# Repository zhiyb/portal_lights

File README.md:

# portal\_lights
Ingress portal lights

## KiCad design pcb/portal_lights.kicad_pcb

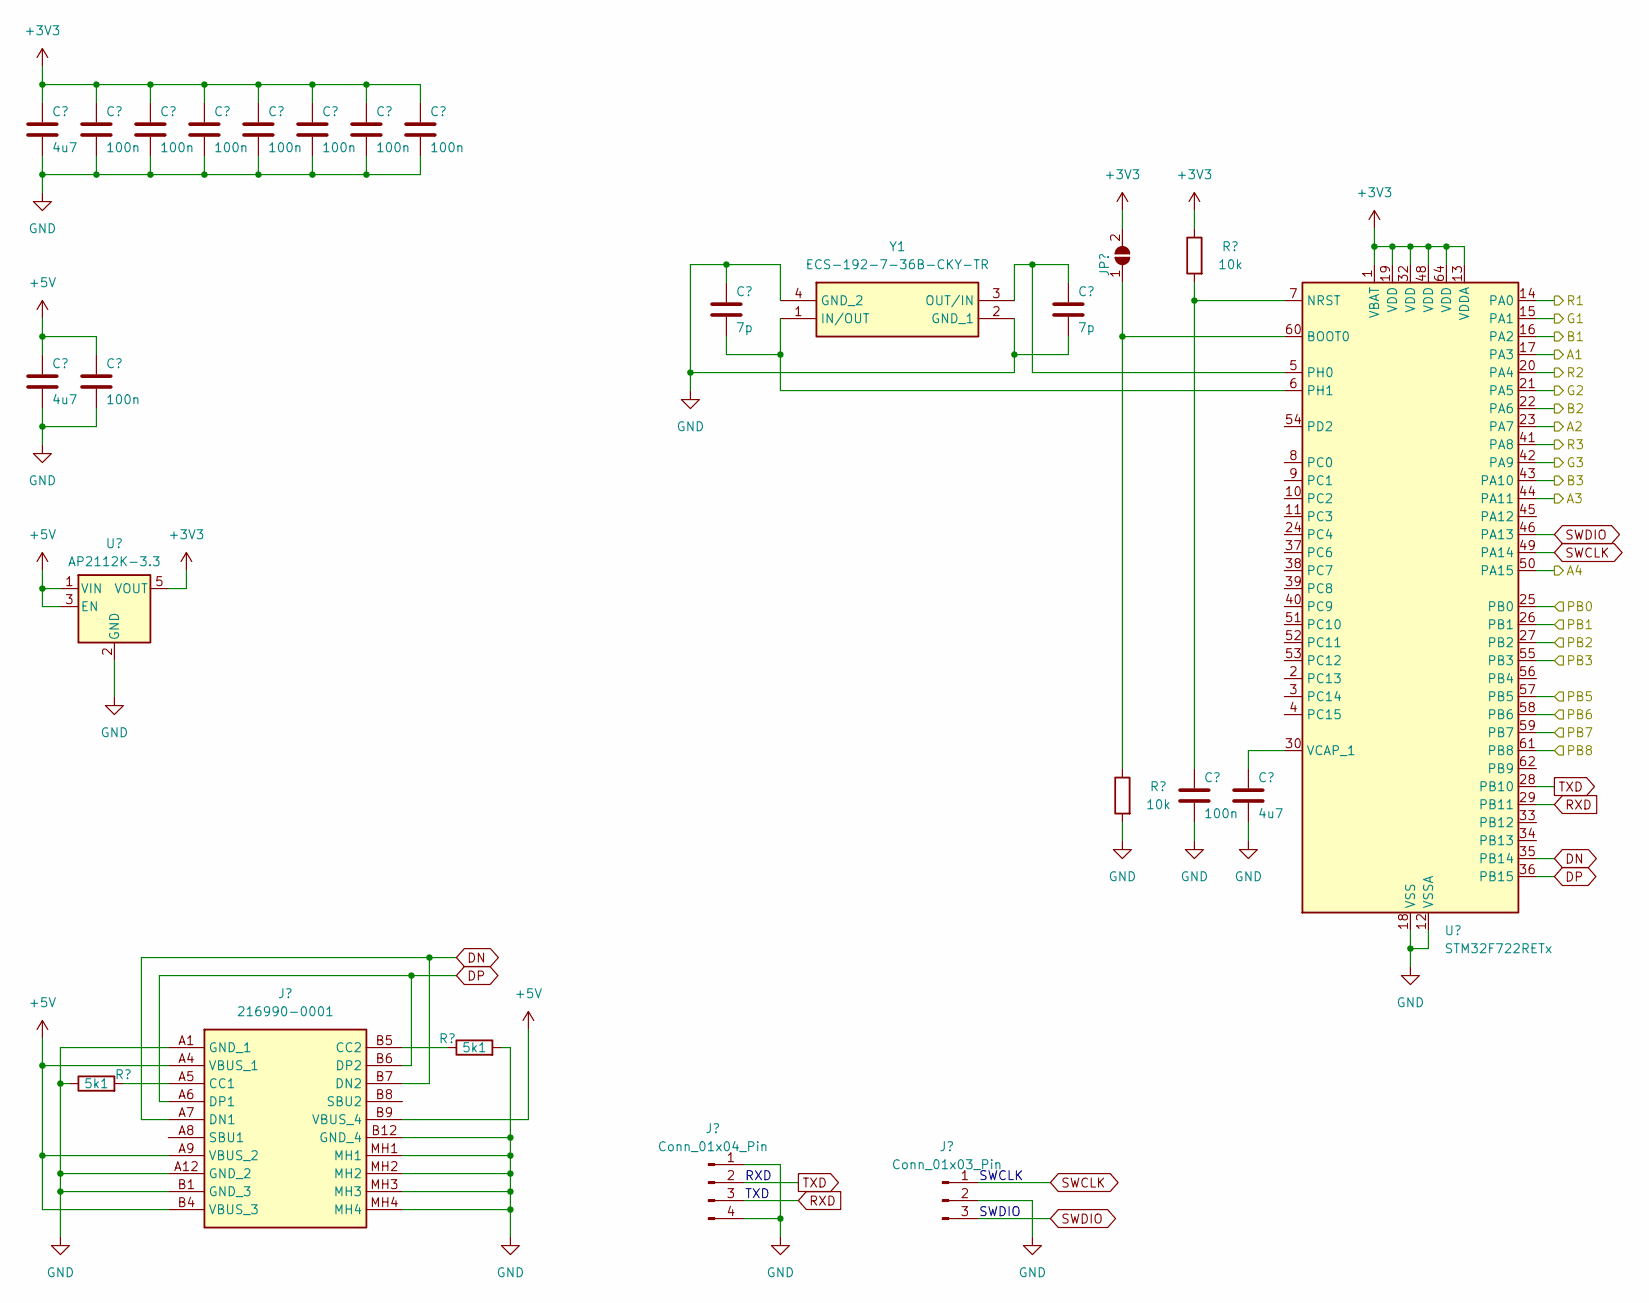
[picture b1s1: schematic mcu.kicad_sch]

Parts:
C1, C11, C14: 4u7; C_0402_1005Metric_Pad0.74x0.62mm_HandSolder
C2, C3, C4, C5, C6, C7, C8, C12, C13: 100n; C_0402_1005Metric_Pad0.74x0.62mm_HandSolder
C9, C10: 7p; C_0402_1005Metric_Pad0.74x0.62mm_HandSolder
J1: 216990-0001; 2169900001; Mouser Part Number 538-216990-0001
J2: Conn_01x04_Pin; PinHeader_1x04_P2.54mm_Vertical
J3: Conn_01x03_Pin; PinHeader_1x03_P2.54mm_Vertical
JP1: SolderJumper_2_Open; SolderJumper-2_P1.3mm_Open_RoundedPad1.0x1.5mm
R1, R2: 10k; R_0402_1005Metric_Pad0.72x0.64mm_HandSolder
R3, R4: 5k1; R_0402_1005Metric_Pad0.72x0.64mm_HandSolder
U1: AP2112K-3.3; SOT-23-5_HandSoldering
U2: STM32F722RETx; LQFP-64_10x10mm_P0.5mm
Y1: ECS-192-7-36B-CKY-TR; ECS192736BCKYTR; Mouser Part Number 520-192-7-36B-CKYT

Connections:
+3V3: C1.1, C2.1, C3.1, C4.1, C5.1, C6.1, C7.1, C8.1, JP1.2 (B), R1.1, U1.5 (VOUT), U2.1 (VBAT), U2.13 (VDDA), U2.19 (VDD), U2.32 (VDD), U2.48 (VDD), U2.64 (VDD); also elsewhere on the board
+5V: C11.1, C12.1, J1.A4 (VBUS_1), J1.A9 (VBUS_2), J1.B4 (VBUS_3), J1.B9 (VBUS_4), U1.1 (VIN), U1.3 (EN)
/IO/PB1: U2.25 (PB0); also elsewhere on the board
/IO/PB2: U2.26 (PB1); also elsewhere on the board
/IO/PB3: U2.27 (PB2); also elsewhere on the board
/IO/PB4: U2.55 (PB3); also elsewhere on the board
/IO/TB1: U2.57 (PB5); also elsewhere on the board
/IO/TB2: U2.58 (PB6); also elsewhere on the board
/IO/TB3: U2.59 (PB7); also elsewhere on the board
/IO/TB4: U2.61 (PB8); also elsewhere on the board
/Lights/A1: U2.17 (PA3); also elsewhere on the board
/Lights/A2: U2.23 (PA7); also elsewhere on the board
/Lights/A3: U2.44 (PA11); also elsewhere on the board
/Lights/A4: U2.50 (PA15); also elsewhere on the board
/Lights/B1: U2.16 (PA2); also elsewhere on the board
/Lights/B2: U2.22 (PA6); also elsewhere on the board
/Lights/B3: U2.43 (PA10); also elsewhere on the board
/Lights/G1: U2.15 (PA1); also elsewhere on the board
/Lights/G2: U2.21 (PA5); also elsewhere on the board
/Lights/G3: U2.42 (PA9); also elsewhere on the board
/Lights/R1: U2.14 (PA0); also elsewhere on the board
/Lights/R2: U2.20 (PA4); also elsewhere on the board
/Lights/R3: U2.41 (PA8); also elsewhere on the board
DN: J1.A7 (DN1), J1.B7 (DN2), U2.35 (PB14)
DP: J1.A6 (DP1), J1.B6 (DP2), U2.36 (PB15)
GND: C1.2, C2.2, C3.2, C4.2, C5.2, C6.2, C7.2, C8.2, C9.1, C10.2, C11.2, C12.2, C13.2, C14.2, J1.A1 (GND_1), J1.A12 (GND_2), J1.B1 (GND_3), J1.B12 (GND_4), J1.MH1, J1.MH2, J1.MH3, J1.MH4, J2.1, J2.4, J3.2, R2.2, R3.2, R4.1, U1.2 (GND), U2.12 (VSSA), U2.18 (VSS), U2.31 (VSS), U2.47 (VSS), U2.63 (VSS), Y1.2 (GND_1), Y1.4 (GND_2); also elsewhere on the board
unnamed: J1.A5 (CC1), R4.2
unnamed: J1.B5 (CC2), R3.1
unnamed: JP1.1 (A), R2.1, U2.60 (BOOT0)
unnamed: C13.1, R1.2, U2.7 (NRST)
unnamed: C10.1, U2.5 (PH0), Y1.3 (OUT/IN)
unnamed: C9.2, U2.6 (PH1), Y1.1 (IN/OUT)
unnamed: C14.1, U2.30 (VCAP_1)
RXD: J2.3, U2.29 (PB11)
SWCLK: J3.1, U2.49 (PA14)
SWDIO: J3.3, U2.46 (PA13)
TXD: J2.2, U2.28 (PB10)

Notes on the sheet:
RXD
SWCLK
TXD
SWDIO

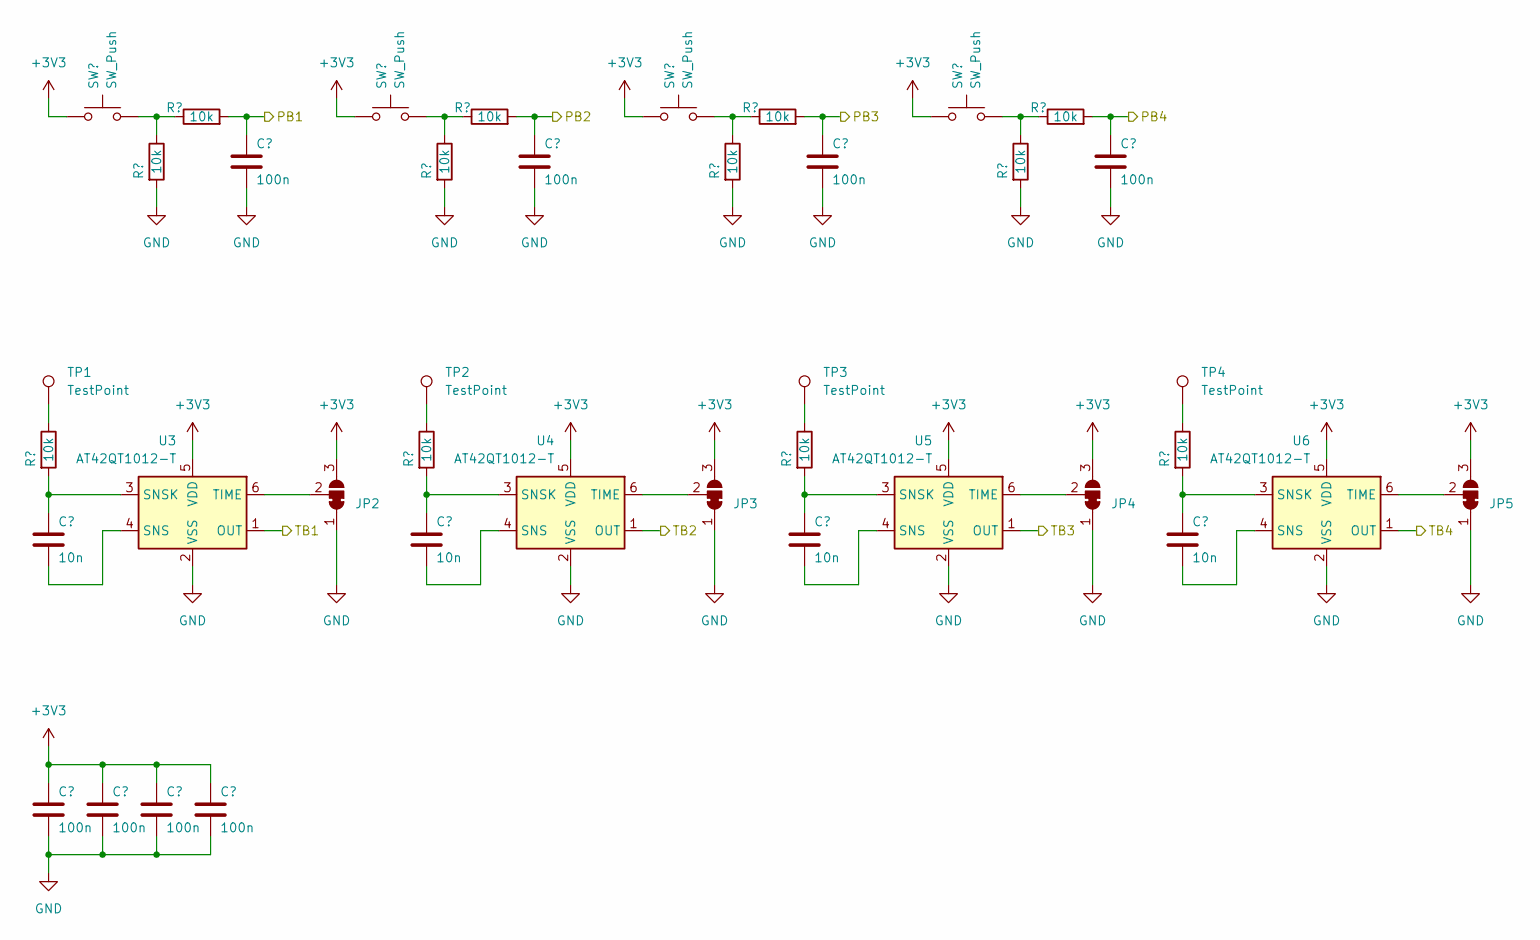
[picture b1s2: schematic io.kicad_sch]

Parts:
C15, C16, C17, C18, C23, C24, C25, C26: 100n; C_0402_1005Metric_Pad0.74x0.62mm_HandSolder
C19, C20, C21, C22: 10n; C_0402_1005Metric_Pad0.74x0.62mm_HandSolder
JP2, JP3, JP4, JP5: SolderJumper_3_Bridged12; SolderJumper-3_P1.3mm_Bridged12_RoundedPad1.0x1.5mm
R5, R6, R7, R8, R9, R10, R11, R12, R13, R14, R15, R16: 10k; R_0402_1005Metric_Pad0.72x0.64mm_HandSolder
SW1, SW2, SW3, SW4: SW_Push; SW_Push_1P1T_NO_6x6mm_H9.5mm
TP1, TP2, TP3, TP4: TestPoint; TestPoint_Pad_D4.0mm
U3, U4, U5, U6: AT42QT1012-T; SOT-23-6

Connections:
+3V3: C23.1, C24.1, C25.1, C26.1, JP2.3 (B), JP3.3 (B), JP4.3 (B), JP5.3 (B), SW1.1, SW2.1, SW3.1, SW4.1, U3.5 (VDD), U4.5 (VDD), U5.5 (VDD), U6.5 (VDD); also elsewhere on the board
/IO/PB1: C15.1, R5.2; also elsewhere on the board
/IO/PB2: C16.1, R6.2; also elsewhere on the board
/IO/PB3: C17.1, R7.2; also elsewhere on the board
/IO/PB4: C18.1, R8.2; also elsewhere on the board
/IO/TB1: U3.1 (OUT); also elsewhere on the board
/IO/TB2: U4.1 (OUT); also elsewhere on the board
/IO/TB3: U5.1 (OUT); also elsewhere on the board
/IO/TB4: U6.1 (OUT); also elsewhere on the board
GND: C15.2, C16.2, C17.2, C18.2, C23.2, C24.2, C25.2, C26.2, JP2.1 (A), JP3.1 (A), JP4.1 (A), JP5.1 (A), R9.2, R10.2, R11.2, R12.2, U3.2 (VSS), U4.2 (VSS), U5.2 (VSS), U6.2 (VSS); also elsewhere on the board
unnamed: JP2.2 (C), U3.6 (TIME)
unnamed: JP3.2 (C), U4.6 (TIME)
unnamed: JP4.2 (C), U5.6 (TIME)
unnamed: JP5.2 (C), U6.6 (TIME)
unnamed: R5.1, R9.1, SW1.2
unnamed: R6.1, R10.1, SW2.2
unnamed: R7.1, R11.1, SW3.2
unnamed: R8.1, R12.1, SW4.2
unnamed: R13.1, TP1.1
unnamed: R14.1, TP2.1
unnamed: R15.1, TP3.1
unnamed: R16.1, TP4.1
unnamed: C19.2, U3.4 (SNS)
unnamed: C19.1, R13.2, U3.3 (SNSK)
unnamed: C20.2, U4.4 (SNS)
unnamed: C20.1, R14.2, U4.3 (SNSK)
unnamed: C21.2, U5.4 (SNS)
unnamed: C21.1, R15.2, U5.3 (SNSK)
unnamed: C22.2, U6.4 (SNS)
unnamed: C22.1, R16.2, U6.3 (SNSK)

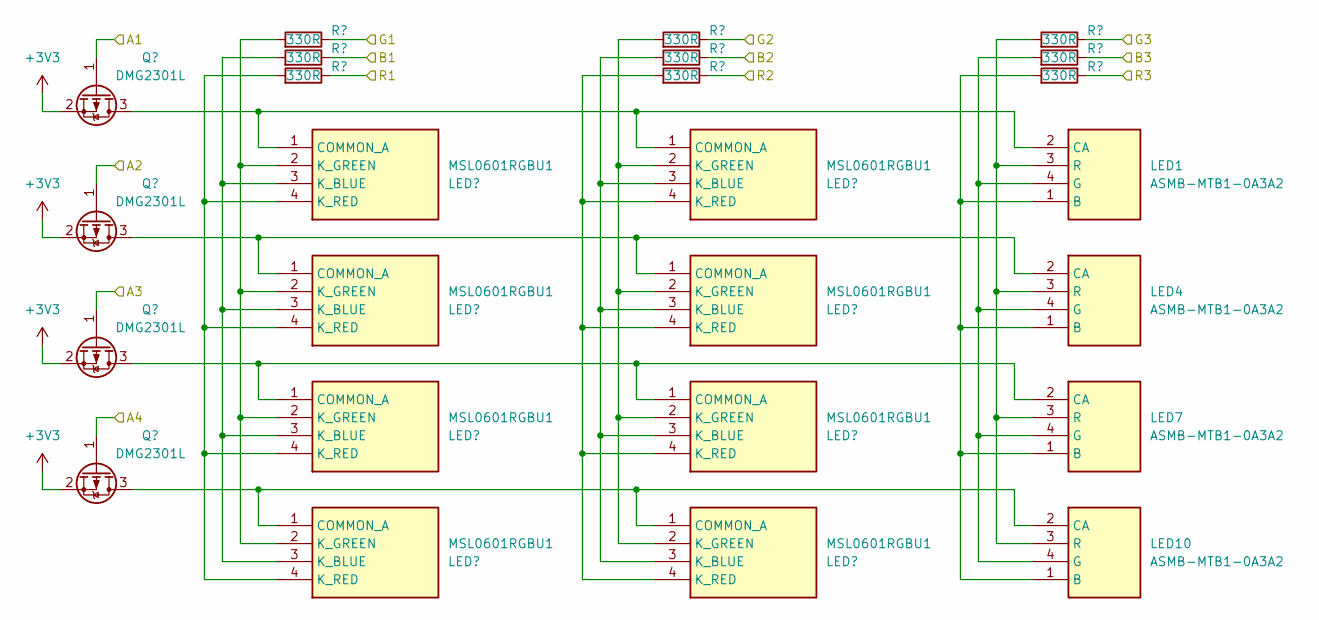
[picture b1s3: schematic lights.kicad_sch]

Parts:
LED1, LED4, LED7, LED10: ASMB-MTB1-0A3A2; HSMFA341A00J1; Mouser Part Number 630-HSMF-A341-A00J1
LED2, LED3, LED5, LED6, LED8, LED9, LED11, LED12: MSL0601RGBU1; Mouser Part Number 755-MSL0601RGBU1
Q1, Q2, Q3, Q4: DMG2301L; SOT-23
R17, R18, R19, R20, R21, R22, R23, R24, R25: 330R; R_0402_1005Metric_Pad0.72x0.64mm_HandSolder

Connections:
+3V3: Q1.2 (S), Q2.2 (S), Q3.2 (S), Q4.2 (S); also elsewhere on the board
/Lights/A1: Q1.1 (G); also elsewhere on the board
/Lights/A2: Q2.1 (G); also elsewhere on the board
/Lights/A3: Q3.1 (G); also elsewhere on the board
/Lights/A4: Q4.1 (G); also elsewhere on the board
/Lights/B1: R20.1; also elsewhere on the board
/Lights/B2: R21.1; also elsewhere on the board
/Lights/B3: R22.1; also elsewhere on the board
/Lights/G1: R17.1; also elsewhere on the board
/Lights/G2: R18.1; also elsewhere on the board
/Lights/G3: R19.1; also elsewhere on the board
/Lights/R1: R23.1; also elsewhere on the board
/Lights/R2: R24.1; also elsewhere on the board
/Lights/R3: R25.1; also elsewhere on the board
unnamed: LED1.1 (B), LED4.1 (B), LED7.1 (B), LED10.1 (B), R25.2
unnamed: LED1.2 (CA), LED2.1 (COMMON_A), LED3.1 (COMMON_A), Q1.3 (D)
unnamed: LED1.4 (G), LED4.4 (G), LED7.4 (G), LED10.4 (G), R22.2
unnamed: LED1.3 (R), LED4.3 (R), LED7.3 (R), LED10.3 (R), R19.2
unnamed: LED4.2 (CA), LED5.1 (COMMON_A), LED6.1 (COMMON_A), Q2.3 (D)
unnamed: LED7.2 (CA), LED8.1 (COMMON_A), LED9.1 (COMMON_A), Q3.3 (D)
unnamed: LED10.2 (CA), LED11.1 (COMMON_A), LED12.1 (COMMON_A), Q4.3 (D)
unnamed: LED2.3 (K_BLUE), LED5.3 (K_BLUE), LED8.3 (K_BLUE), LED11.3 (K_BLUE), R20.2
unnamed: LED2.2 (K_GREEN), LED5.2 (K_GREEN), LED8.2 (K_GREEN), LED11.2 (K_GREEN), R17.2
unnamed: LED2.4 (K_RED), LED5.4 (K_RED), LED8.4 (K_RED), LED11.4 (K_RED), R23.2
unnamed: LED3.3 (K_BLUE), LED6.3 (K_BLUE), LED9.3 (K_BLUE), LED12.3 (K_BLUE), R21.2
unnamed: LED3.2 (K_GREEN), LED6.2 (K_GREEN), LED9.2 (K_GREEN), LED12.2 (K_GREEN), R18.2
unnamed: LED3.4 (K_RED), LED6.4 (K_RED), LED9.4 (K_RED), LED12.4 (K_RED), R24.2

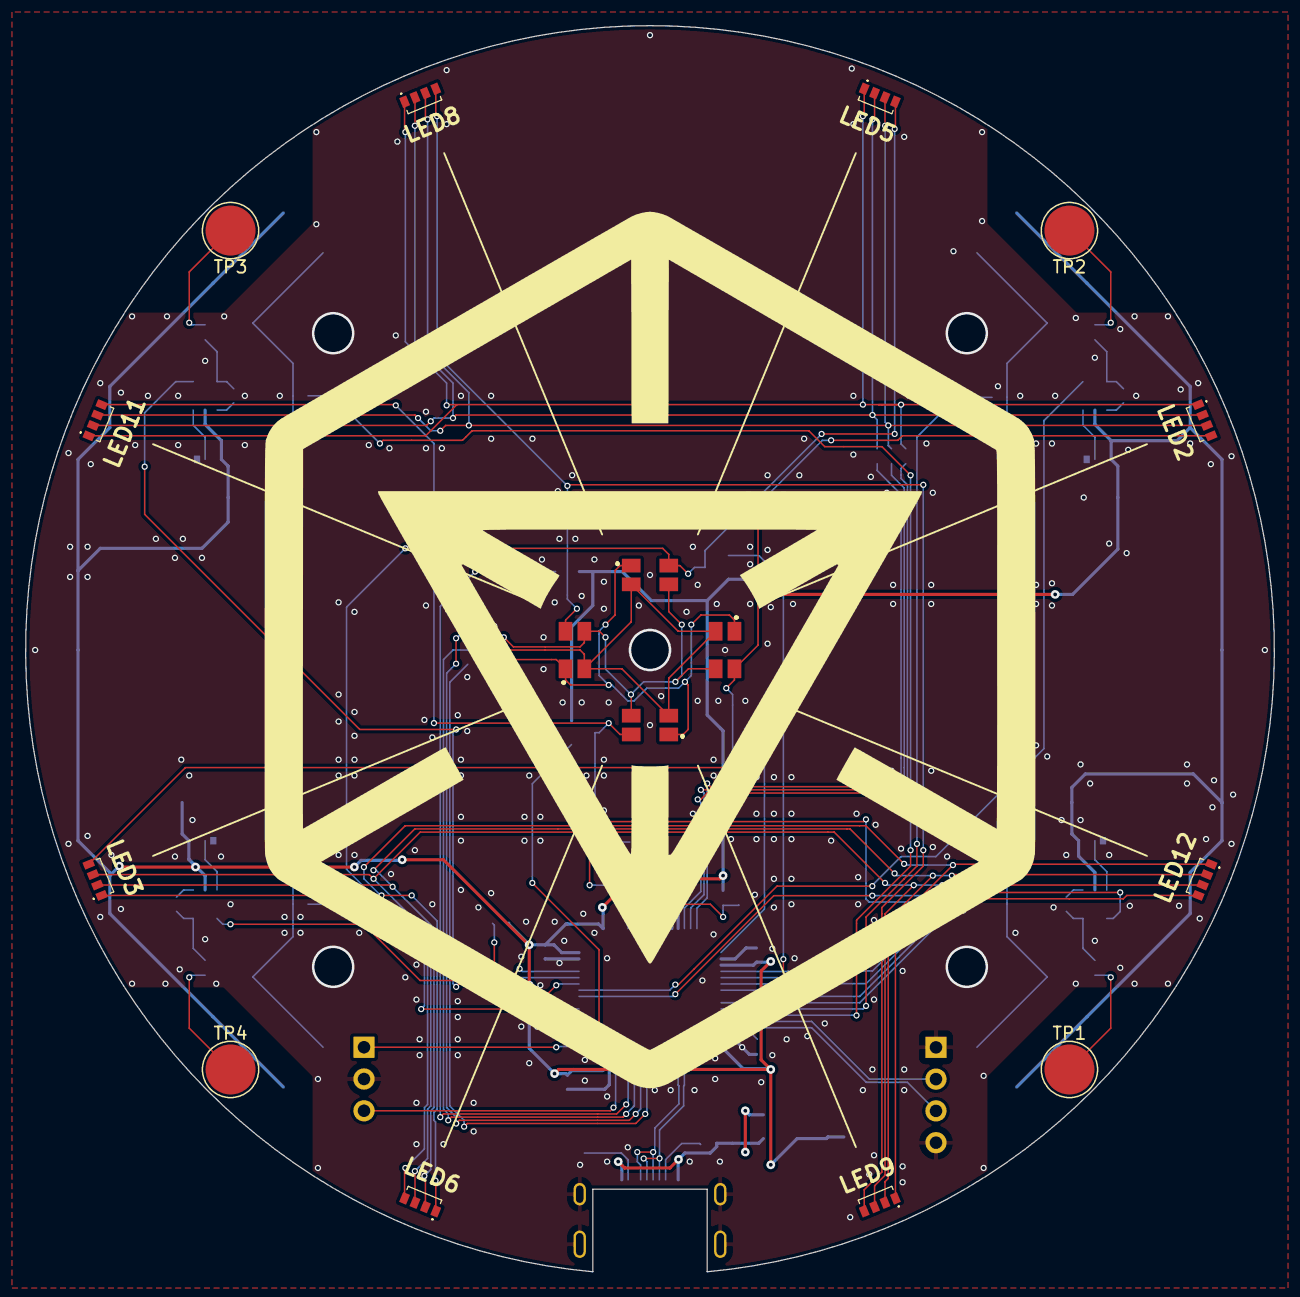
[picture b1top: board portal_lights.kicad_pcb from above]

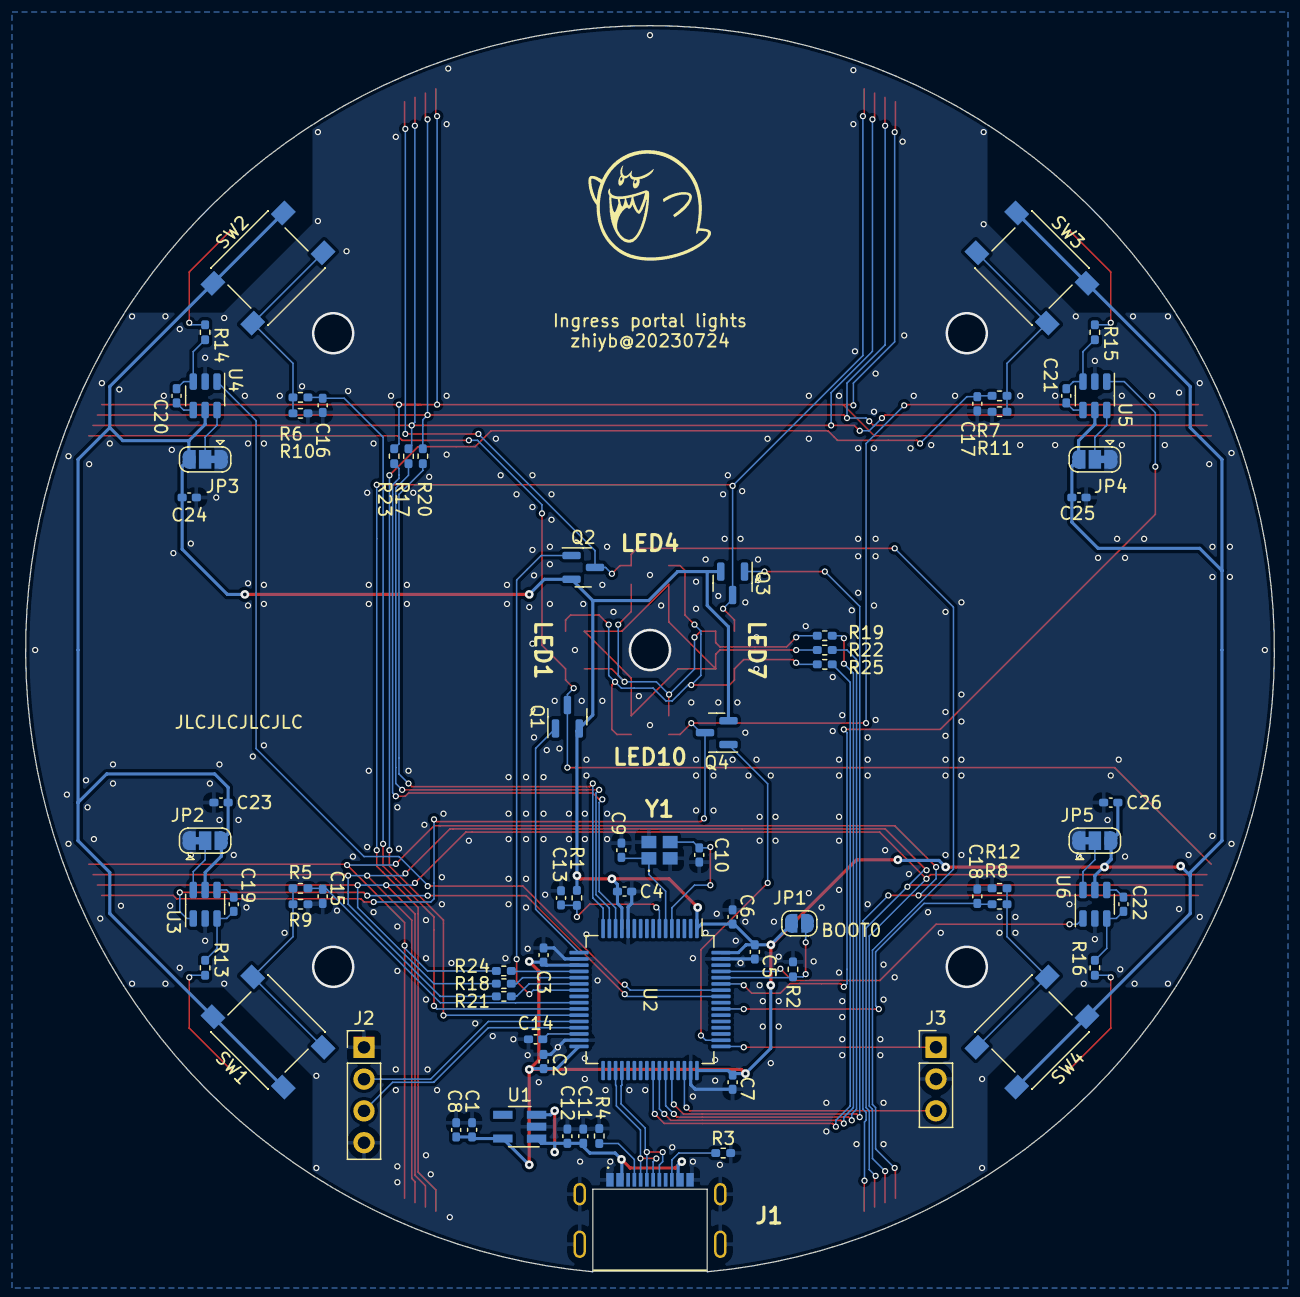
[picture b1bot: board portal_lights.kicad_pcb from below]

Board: 2 copper layers, 99.8 x 99.6 mm, 90 parts (74 on the bottom side), 70 nets.

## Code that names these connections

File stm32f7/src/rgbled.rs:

//use paste::paste;
use core::mem::MaybeUninit;

//use cortex_m::asm;
use stm32f7::stm32f7x2::Peripherals;

use crate::config::CONFIG;
use crate::utility::{GAMMA4_1024, HCL_LUT};

// RGB LED matrix connections:
//
// PA0  -> R1
// PA1  -> G1
// PA2  -> B1
//
// PA4  -> R2
// PA5  -> G2
// PA6  -> B2
//
// PA9  -> R3
// PA10 -> G3
// PA8  -> B3
//
// PA3  -> A1
// PA7  -> A2
// PA11 -> A3
// PA15 -> A4

const LED_NUM: usize = 12;

// Allocated DMA RAM for refreshing LEDs
const LED_GREYSCALE: usize = 1024;
const LED_SCAN_OFF:  usize = 1;
const LED_SCAN_ROWS: usize = 4;
const LED_SCAN_SIZE: usize = LED_SCAN_ROWS * (LED_GREYSCALE + LED_SCAN_OFF);

#[link_section = ".dmaram"]
static mut LED_RAM: MaybeUninit<[[u16; LED_GREYSCALE + LED_SCAN_OFF]; LED_SCAN_ROWS]> = MaybeUninit::uninit();

// Current LED states
static mut LED_COLOUR: [[u8; 3]; LED_NUM] = [[0; 3]; LED_NUM];

// GPIO update rate
const LED_GPIO_RATE: usize = LED_SCAN_SIZE * 480;

/// Initialise RGB LED matrix
pub fn rgbled_init(p: &Peripherals) {
    // Power on GPIOA bank
    p.RCC.ahb1enr.modify(|_, w| w.gpioaen().set_bit());
    // Configure GPIOA bank, IO in output mode
    p.GPIOA.odr.modify(|_, w| w
        .odr0 ().high()
        .odr1 ().high()
        .odr2 ().high()
        .odr3 ().high()
        .odr4 ().high()
        .odr5 ().high()
        .odr6 ().high()
        .odr7 ().high()
        .odr8 ().high()
        .odr9 ().high()
        .odr10().high()
        .odr11().high()
        .odr15().high());
    p.GPIOA.moder.modify(|_, w| w
        .moder0 ().output()
        .moder1 ().output()
        .moder2 ().output()
        .moder3 ().output()
        .moder4 ().output()
        .moder5 ().output()
        .moder6 ().output()
        .moder7 ().output()
        .moder8 ().output()
        .moder9 ().output()
        .moder10().output()
        .moder11().output()
        .moder15().output());
    p.GPIOA.otyper.modify(|_, w| w
        .ot0 ().push_pull()
        .ot1 ().push_pull()
        .ot2 ().push_pull()
        .ot3 ().push_pull()
        .ot4 ().push_pull()
        .ot5 ().push_pull()
        .ot6 ().push_pull()
        .ot7 ().push_pull()
        .ot8 ().push_pull()
        .ot9 ().push_pull()
        .ot10().push_pull()
        .ot11().push_pull()
        .ot15().push_pull());
    p.GPIOA.pupdr.modify(|_, w| w
        .pupdr0 ().floating()
        .pupdr1 ().floating()
        .pupdr2 ().floating()
        .pupdr3 ().floating()
        .pupdr4 ().floating()
        .pupdr5 ().floating()
        .pupdr6 ().floating()
        .pupdr7 ().floating()
        .pupdr8 ().floating()
        .pupdr9 ().floating()
        .pupdr10().floating()
        .pupdr11().floating()
        .pupdr15().floating());
    p.GPIOA.ospeedr.modify(|_, w| w
        .ospeedr0 ().low_speed()
        .ospeedr1 ().low_speed()
        .ospeedr2 ().low_speed()
        .ospeedr3 ().low_speed()
        .ospeedr4 ().low_speed()
        .ospeedr5 ().low_speed()
        .ospeedr6 ().low_speed()
        .ospeedr7 ().low_speed()
        .ospeedr8 ().low_speed()
        .ospeedr9 ().low_speed()
        .ospeedr10().low_speed()
        .ospeedr11().low_speed()
        .ospeedr15().low_speed());

    // Use DMA2 stream 1 Channel 7 to transfer LED refresh data to GPIO
    // DMA request trigger is TIM8_UP

    // Initialised DMA2 stream 1 Channel 7
    let dma = &p.DMA2;
    let dmast = &p.DMA2.st[1];
    p.RCC.ahb1enr.modify(|_, w| w.dma2en().enabled());
    dmast.cr.write(|w| w.en().disabled());
	// Clear DMA flags
    dma.lifcr.write(|w| w
        .ctcif1().clear()
        .chtif1().clear()
        .cteif1().clear()
        .cdmeif1().clear()
        .cfeif1().clear());
    // Memory to peripheral, circular, 32bit -> 16bit, very high priority
    dmast.cr.write(|w| w
        .chsel().bits(7)
        .mburst().single()
        .pburst().single()
        .dbm().disabled()
        .pl().very_high()
        .msize().bits32()
        .psize().bits16()
        .minc().incremented()
        .pinc().fixed()
        .circ().enabled()
        .dir().memory_to_peripheral()
        .pfctrl().dma()
        .tcie().disabled()
        .htie().disabled()
        .teie().disabled()
        .dmeie().disabled()
        .en().disabled());
	// FIFO control
    dmast.fcr.write(|w| w
        .dmdis().disabled()
        .fth().full()
        .feie().disabled());
    // Peripheral address
    dmast.par.write(|w| unsafe {w.pa().bits(p.GPIOA.odr.as_ptr() as u32)});
	// Memory address
    dmast.m0ar.write(|w| unsafe {w.m0a().bits(LED_RAM.as_mut_ptr() as u32)});
	// Number of data items
    dmast.ndtr.write(|w| w.ndt().bits(LED_SCAN_SIZE as u16));

    // Initialise timer 8
    let tim = &p.TIM8;
    p.RCC.apb2enr.modify(|_, w| w.tim8en().enabled());
    tim.cr1.write(|w| w.cen().disabled());
	// Auto reload buffered, edge-align mode, continuous
    tim.cr1.write(|w| w
        .ckd().div1()
        .arpe().enabled()
        .cms().edge_aligned()
        .dir().up()
        .opm().disabled()
        .urs().counter_only()
        .udis().enabled()
        .cen().disabled());
    // Prescaler div 1
    tim.psc.write(|w| w.psc().bits(0));
    // Timer overflow value
    tim.arr.write(|w| w.arr().bits((CONFIG.apb2timclk_rate / LED_GPIO_RATE as u32) as u16));
    // No repetition counter
    tim.rcr.reset();
    // No trigger output
    tim.cr2.reset();
    // Not slave mode
    tim.smcr.reset();
    // Break function disable
    tim.bdtr.reset();
    // Disable CC channels
    tim.ccmr1_output().reset();
    tim.ccmr2_output().reset();
    tim.ccer.reset();
    // Enable DMA request from update event, disable interrupts
    tim.dier.write(|w| w.ude().enabled());
    // Reset counter values
    tim.cnt.reset();

    // Initialise DMA RAM
    rgbled_init_ram();

    // Enable DMA and timer
    dmast.cr.modify(|_, w| w.en().enabled());
    tim.cr1.modify(|_, w| w.cen().enabled());
}

const fn scan_value(rgb: [(bool, bool, bool); 3], row: u16) -> u16 {
    let r1 = !rgb[0].0 as u16;
    let g1 = !rgb[0].1 as u16;
    let b1 = !rgb[0].2 as u16;
    let r2 = !rgb[1].0 as u16;
    let g2 = !rgb[1].1 as u16;
    let b2 = !rgb[1].2 as u16;
    let r3 = !rgb[2].0 as u16;
    let g3 = !rgb[2].1 as u16;
    let b3 = !rgb[2].2 as u16;
    // Interleaved scan rows
    let a1 = (!row >> 0) & 1;
    let a2 = (!row >> 2) & 1;
    let a3 = (!row >> 1) & 1;
    let a4 = (!row >> 3) & 1;
    return (r1 << 0) | (g1 << 1) | (b1 << 2)
        | (r2 << 4) | (g2 << 5) | (b2 << 6)
        | (r3 << 9) | (g3 << 10) | (b3 << 8)
        | (a1 << 3) | (a2 << 7) | (a3 << 11) | (a4 << 15);
}

fn rgbled_init_ram() {
    // Clear LED greyscale RAM buffer
    let disabled = scan_value([
        (false, false, false),
        (false, false, false),
        (false, false, false),
        ], 0);
    // Extra greyscale entries for disabling LED outputs before row switch
    unsafe {LED_RAM.write([[disabled; LED_GREYSCALE + LED_SCAN_OFF]; LED_SCAN_ROWS]);}
}

fn rgbled_update_row(mut row: usize) {
    let ram = unsafe {LED_RAM.assume_init_mut()};
    let mut led: [[u16; 3]; 3] = [[0; 3]; 3];
    for i in 0 .. 3 {
        for c in 0 .. 3 {
            led[i][c] = GAMMA4_1024[unsafe {LED_COLOUR[row + 4 * i][c]} as usize];
        }
    }
    row = [0, 2, 1, 3][row];
    for gs in 0 ..= LED_GREYSCALE as u16 {
        ram[row][gs as usize] = scan_value([
            (led[0][0] > gs, led[0][1] > gs, led[0][2] > gs),
            (led[1][0] > gs, led[1][1] > gs, led[1][2] > gs),
            (led[2][0] > gs, led[2][1] > gs, led[2][2] > gs),
            ], 1 << row);
    }
}

pub fn rgbled_set(n: usize, rgb: [u8; 3]) {
    assert!(n < LED_NUM);
    unsafe {LED_COLOUR[n as usize] = rgb;}
    rgbled_update_row((n % 4) as usize);
}

pub fn rgbled_set_all(rgb: [[u8; 3]; LED_NUM]) {
    unsafe {LED_COLOUR = rgb;}
    for i in 0 .. LED_SCAN_ROWS {
        rgbled_update_row(i);
    }
}

pub fn rgbled_test(n: usize, i: u32) {
    //let colour = HCL_LUT[(i as usize * HCL_LUT.len() / 2000) % HCL_LUT.len()];
    let colour = HCL_LUT[i as usize % HCL_LUT.len()];

    let mut rgb;
    if true {
        rgb = [[0u8; 3]; LED_NUM];
        if n == 0 {
            for c in &mut rgb {
                *c = colour;
            }
        } else {
            let nled = (n - 1) % LED_NUM;
            rgb[nled] = colour;
        }

    } else {
        let nled = n % LED_NUM;
        rgb = unsafe {LED_COLOUR};
        rgb[nled] = colour;
    }

    rgbled_set_all(rgb);
}

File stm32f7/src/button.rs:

use stm32f7::stm32f7x2::Peripherals;

// Button connections:
//
// PB0 -> Button 1
// PB1 -> Button 2
// PB2 -> Button 3
// PB3 -> Button 4
//
// PB5 -> Touch 1
// PB6 -> Touch 2
// PB7 -> Touch 3
// PB8 -> Touch 4

/// Initialise buttons
pub fn button_init(p: &Peripherals) {
    // Power on GPIOB bank
    p.RCC.ahb1enr.modify(|_, w| w.gpioben().set_bit());
    // Configure GPIOB bank, IO in floating input mode
    p.GPIOB.moder.modify(|_, w| w
        .moder0 ().input()
        .moder1 ().input()
        .moder2 ().input()
        .moder3 ().input()
        .moder5 ().input()
        .moder6 ().input()
        .moder7 ().input()
        .moder8 ().input());
    p.GPIOB.pupdr.modify(|_, w| w
        .pupdr0 ().floating()
        .pupdr1 ().floating()
        .pupdr2 ().floating()
        .pupdr3 ().floating()
        .pupdr5 ().floating()
        .pupdr6 ().floating()
        .pupdr7 ().floating()
        .pupdr8 ().floating());
}

pub fn button_read(p: &Peripherals) -> u32 {
    let v = p.GPIOB.idr.read().bits();
    return ((v << 4) & 0xf0) | ((v >> 5) & 0x0f);
}

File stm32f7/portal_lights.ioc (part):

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Mcu.Name=STM32F722R(C-E)Tx
Mcu.Package=LQFP64
Mcu.UserName=STM32F722RETx
PA13.Mode=Serial_Wire
PA13.Signal=SYS_JTMS-SWDIO
PA14.Mode=Serial_Wire
PA14.Signal=SYS_JTCK-SWCLK
PB10.Mode=Asynchronous
PB10.Signal=USART3_TX
PB11.Mode=Asynchronous
PB11.Signal=USART3_RX
PB14.Mode=Internal_Phy_Device
PB14.Signal=USB_OTG_HS_DM
PB15.Mode=Internal_Phy_Device
PB15.Signal=USB_OTG_HS_DP
PH0-OSC_IN.Mode=HSE-External-Oscillator
PH0-OSC_IN.Signal=RCC_OSC_IN
PH1-OSC_OUT.Mode=HSE-External-Oscillator
PH1-OSC_OUT.Signal=RCC_OSC_OUT
RCC.HSE_VALUE=19200000
RCC.SYSCLKFreq_VALUE=216000000
RCC.SYSCLKSource=RCC_SYSCLKSOURCE_PLLCLK
board=custom

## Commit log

2023-07-23 portal_lights initial design
2023-07-24 Updates for release v20230724
2023-08-04 Fix RGB LED part # should be ASMB-MTB1-0A3A2
2023-08-04 Move PCB design to pcb subdirectory
2023-08-05 stm32f7: Rust initial project
2023-08-05 stm32f7: Add STM32 CubeMX project file for reference
2023-08-05 stm32f7: rcc initialisation
2023-08-05 stm32f7: Initial support for multiple linker scripts, bootloader
2023-08-05 pcb: Some notes about incorrect RGB LED footprint and connection
2023-08-05 stm32f7: Minimal bootloader, RGB LED tests
2023-08-05 stm32f7: Button GPIO inputs
2023-08-06 stm32f7: RGB LED scan initial implementation using DMA
2023-08-06 stm32f7: Move some functions to utility.rs
2023-08-06 stm32f7: Increase LED greyscale to 1024 levels
